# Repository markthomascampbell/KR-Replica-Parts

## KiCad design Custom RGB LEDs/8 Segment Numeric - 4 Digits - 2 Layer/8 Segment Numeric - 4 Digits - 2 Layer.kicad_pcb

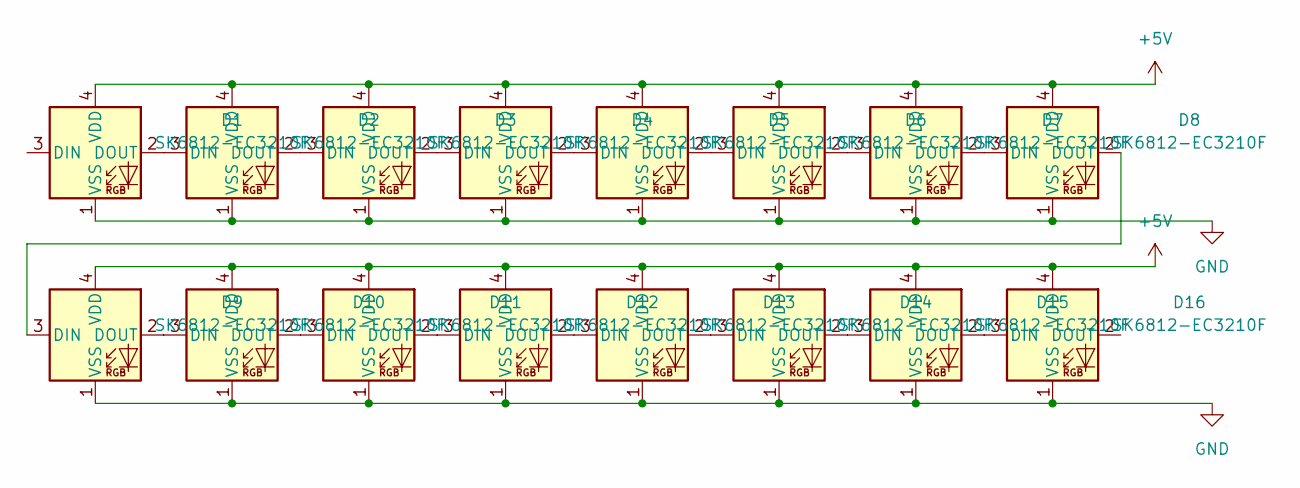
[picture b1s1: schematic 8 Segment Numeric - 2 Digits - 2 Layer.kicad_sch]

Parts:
D1, D2, D3, D4, D5, D6, D7, D8, D9, D10, D11, D12, D13, D14, D15, D16: SK6812-EC3210F

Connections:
+5V: D1.4 (VDD), D2.4 (VDD), D3.4 (VDD), D4.4 (VDD), D5.4 (VDD), D6.4 (VDD), D7.4 (VDD), D8.4 (VDD), D9.4 (VDD), D10.4 (VDD), D11.4 (VDD), D12.4 (VDD), D13.4 (VDD), D14.4 (VDD), D15.4 (VDD), D16.4 (VDD); also elsewhere on the board
GND: D1.1 (VSS), D2.1 (VSS), D3.1 (VSS), D4.1 (VSS), D5.1 (VSS), D6.1 (VSS), D7.1 (VSS), D8.1 (VSS), D9.1 (VSS), D10.1 (VSS), D11.1 (VSS), D12.1 (VSS), D13.1 (VSS), D14.1 (VSS), D15.1 (VSS), D16.1 (VSS); also elsewhere on the board
unnamed: D1.2 (DOUT), D2.3 (DIN)
unnamed: D2.2 (DOUT), D3.3 (DIN)
unnamed: D3.2 (DOUT), D4.3 (DIN)
unnamed: D4.2 (DOUT), D5.3 (DIN)
unnamed: D5.2 (DOUT), D6.3 (DIN)
unnamed: D6.2 (DOUT), D7.3 (DIN)
unnamed: D7.2 (DOUT), D8.3 (DIN)
unnamed: D8.2 (DOUT), D9.3 (DIN)
unnamed: D9.2 (DOUT), D10.3 (DIN)
unnamed: D10.2 (DOUT), D11.3 (DIN)
unnamed: D11.2 (DOUT), D12.3 (DIN)
unnamed: D12.2 (DOUT), D13.3 (DIN)
unnamed: D13.2 (DOUT), D14.3 (DIN)
unnamed: D14.2 (DOUT), D15.3 (DIN)
unnamed: D15.2 (DOUT), D16.3 (DIN)
unnamed 17: D16.2 (DOUT); also elsewhere on the board

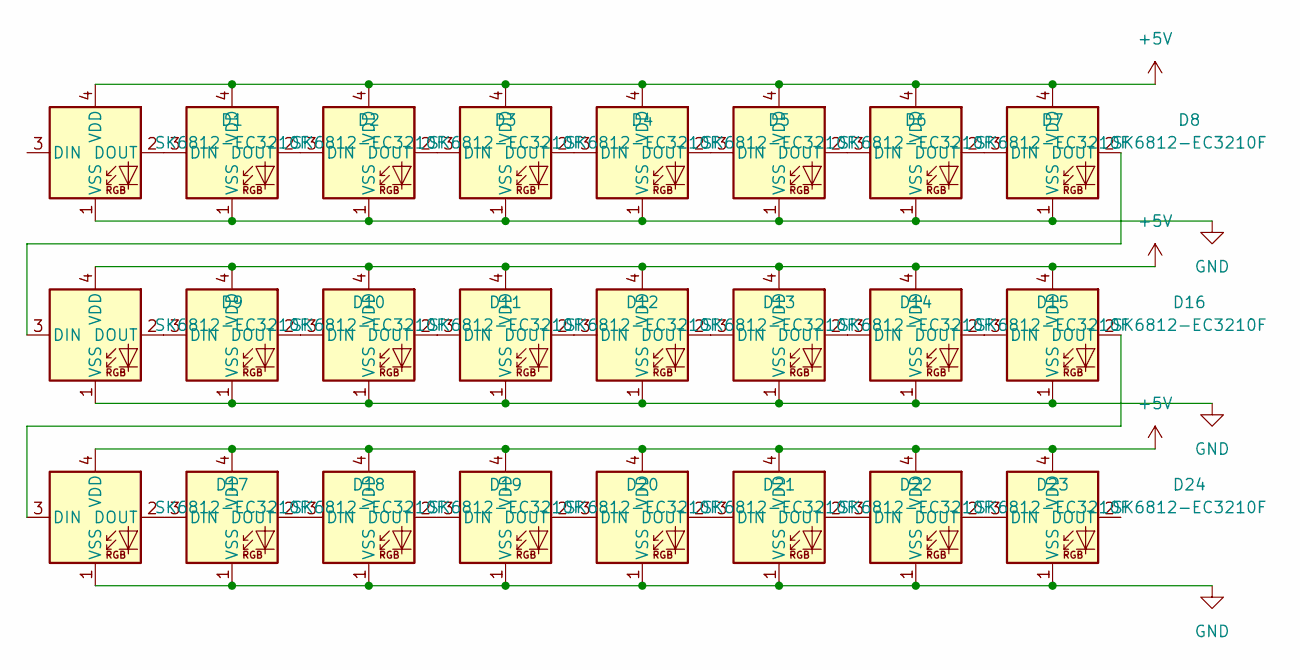
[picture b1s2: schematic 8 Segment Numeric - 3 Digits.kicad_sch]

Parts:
D1, D2, D3, D4, D5, D6, D7, D8, D9, D10, D11, D12, D13, D14, D15, D16, D17, D18, D19, D20, D21, D22, D23, D24: SK6812-EC3210F

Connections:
+5V: D1.4 (VDD), D2.4 (VDD), D3.4 (VDD), D4.4 (VDD), D5.4 (VDD), D6.4 (VDD), D7.4 (VDD), D8.4 (VDD), D9.4 (VDD), D10.4 (VDD), D11.4 (VDD), D12.4 (VDD), D13.4 (VDD), D14.4 (VDD), D15.4 (VDD), D16.4 (VDD), D17.4 (VDD), D18.4 (VDD), D19.4 (VDD), D20.4 (VDD), D21.4 (VDD), D22.4 (VDD), D23.4 (VDD), D24.4 (VDD); also elsewhere on the board
GND: D1.1 (VSS), D2.1 (VSS), D3.1 (VSS), D4.1 (VSS), D5.1 (VSS), D6.1 (VSS), D7.1 (VSS), D8.1 (VSS), D9.1 (VSS), D10.1 (VSS), D11.1 (VSS), D12.1 (VSS), D13.1 (VSS), D14.1 (VSS), D15.1 (VSS), D16.1 (VSS), D17.1 (VSS), D18.1 (VSS), D19.1 (VSS), D20.1 (VSS), D21.1 (VSS), D22.1 (VSS), D23.1 (VSS), D24.1 (VSS); also elsewhere on the board
unnamed: D1.2 (DOUT), D2.3 (DIN)
unnamed: D2.2 (DOUT), D3.3 (DIN)
unnamed: D3.2 (DOUT), D4.3 (DIN)
unnamed: D4.2 (DOUT), D5.3 (DIN)
unnamed: D5.2 (DOUT), D6.3 (DIN)
unnamed: D6.2 (DOUT), D7.3 (DIN)
unnamed: D7.2 (DOUT), D8.3 (DIN)
unnamed: D8.2 (DOUT), D9.3 (DIN)
unnamed: D9.2 (DOUT), D10.3 (DIN)
unnamed: D10.2 (DOUT), D11.3 (DIN)
unnamed: D11.2 (DOUT), D12.3 (DIN)
unnamed: D12.2 (DOUT), D13.3 (DIN)
unnamed: D13.2 (DOUT), D14.3 (DIN)
unnamed: D14.2 (DOUT), D15.3 (DIN)
unnamed: D15.2 (DOUT), D16.3 (DIN)
unnamed: D16.2 (DOUT), D17.3 (DIN)
unnamed: D17.2 (DOUT), D18.3 (DIN)
unnamed: D18.2 (DOUT), D19.3 (DIN)
unnamed: D19.2 (DOUT), D20.3 (DIN)
unnamed: D20.2 (DOUT), D21.3 (DIN)
unnamed: D21.2 (DOUT), D22.3 (DIN)
unnamed: D22.2 (DOUT), D23.3 (DIN)
unnamed: D23.2 (DOUT), D24.3 (DIN)
unnamed 25: D24.2 (DOUT); also elsewhere on the board

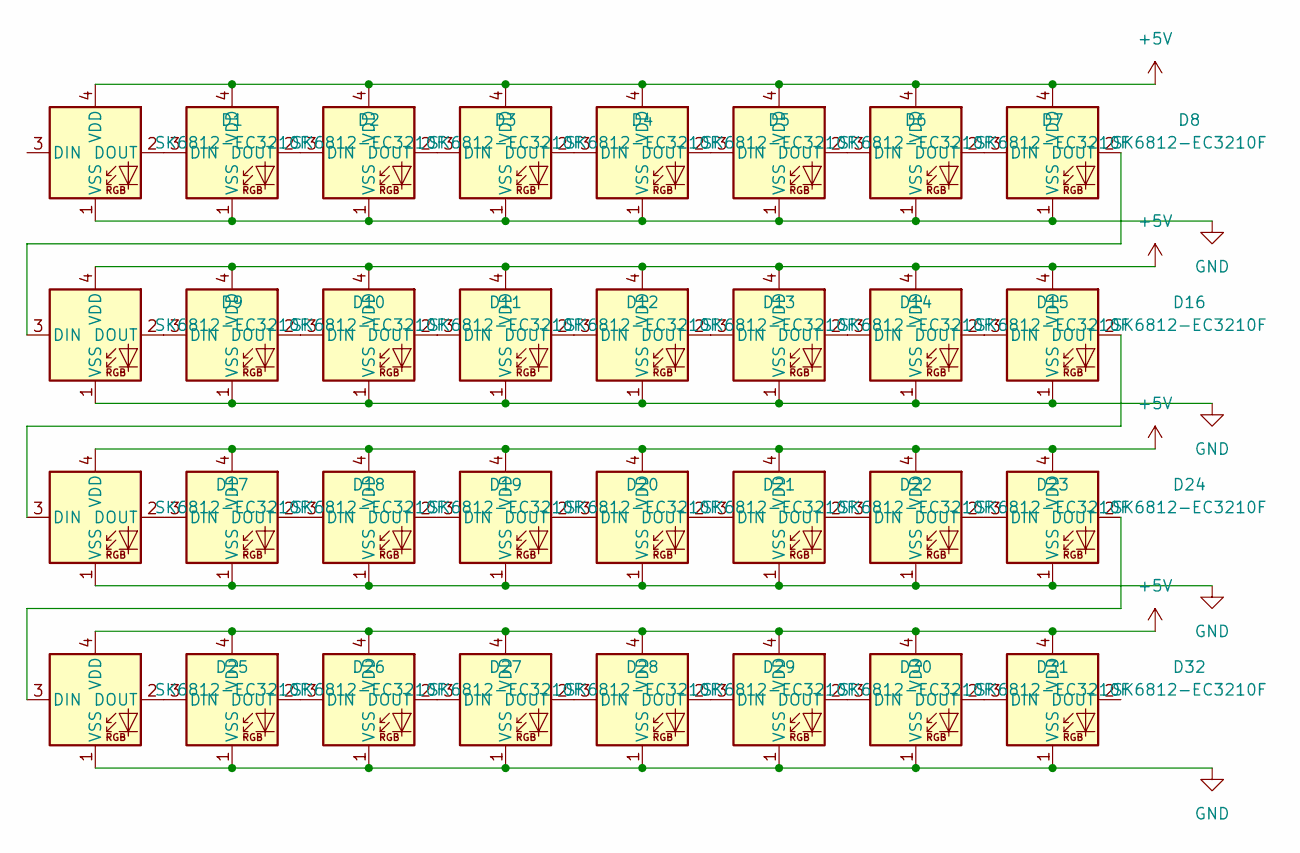
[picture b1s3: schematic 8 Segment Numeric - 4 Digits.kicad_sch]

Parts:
D1, D2, D3, D4, D5, D6, D7, D8, D9, D10, D11, D12, D13, D14, D15, D16, D17, D18, D19, D20, D21, D22, D23, D24, D25, D26, D27, D28, D29, D30, D31, D32: SK6812-EC3210F

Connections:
+5V: D1.4 (VDD), D2.4 (VDD), D3.4 (VDD), D4.4 (VDD), D5.4 (VDD), D6.4 (VDD), D7.4 (VDD), D8.4 (VDD), D9.4 (VDD), D10.4 (VDD), D11.4 (VDD), D12.4 (VDD), D13.4 (VDD), D14.4 (VDD), D15.4 (VDD), D16.4 (VDD), D17.4 (VDD), D18.4 (VDD), D19.4 (VDD), D20.4 (VDD), D21.4 (VDD), D22.4 (VDD), D23.4 (VDD), D24.4 (VDD), D25.4 (VDD), D26.4 (VDD), D27.4 (VDD), D28.4 (VDD), D29.4 (VDD), D30.4 (VDD), D31.4 (VDD), D32.4 (VDD); also elsewhere on the board
GND: D1.1 (VSS), D2.1 (VSS), D3.1 (VSS), D4.1 (VSS), D5.1 (VSS), D6.1 (VSS), D7.1 (VSS), D8.1 (VSS), D9.1 (VSS), D10.1 (VSS), D11.1 (VSS), D12.1 (VSS), D13.1 (VSS), D14.1 (VSS), D15.1 (VSS), D16.1 (VSS), D17.1 (VSS), D18.1 (VSS), D19.1 (VSS), D20.1 (VSS), D21.1 (VSS), D22.1 (VSS), D23.1 (VSS), D24.1 (VSS), D25.1 (VSS), D26.1 (VSS), D27.1 (VSS), D28.1 (VSS), D29.1 (VSS), D30.1 (VSS), D31.1 (VSS), D32.1 (VSS); also elsewhere on the board
unnamed: D1.2 (DOUT), D2.3 (DIN)
unnamed: D2.2 (DOUT), D3.3 (DIN)
unnamed: D3.2 (DOUT), D4.3 (DIN)
unnamed: D4.2 (DOUT), D5.3 (DIN)
unnamed: D5.2 (DOUT), D6.3 (DIN)
unnamed: D6.2 (DOUT), D7.3 (DIN)
unnamed: D7.2 (DOUT), D8.3 (DIN)
unnamed: D8.2 (DOUT), D9.3 (DIN)
unnamed: D9.2 (DOUT), D10.3 (DIN)
unnamed: D10.2 (DOUT), D11.3 (DIN)
unnamed: D11.2 (DOUT), D12.3 (DIN)
unnamed: D12.2 (DOUT), D13.3 (DIN)
unnamed: D13.2 (DOUT), D14.3 (DIN)
unnamed: D14.2 (DOUT), D15.3 (DIN)
unnamed: D15.2 (DOUT), D16.3 (DIN)
unnamed: D16.2 (DOUT), D17.3 (DIN)
unnamed: D17.2 (DOUT), D18.3 (DIN)
unnamed: D18.2 (DOUT), D19.3 (DIN)
unnamed: D19.2 (DOUT), D20.3 (DIN)
unnamed: D20.2 (DOUT), D21.3 (DIN)
unnamed: D21.2 (DOUT), D22.3 (DIN)
unnamed: D22.2 (DOUT), D23.3 (DIN)
unnamed: D23.2 (DOUT), D24.3 (DIN)
unnamed: D24.2 (DOUT), D25.3 (DIN)
unnamed: D25.2 (DOUT), D26.3 (DIN)
unnamed: D26.2 (DOUT), D27.3 (DIN)
unnamed: D27.2 (DOUT), D28.3 (DIN)
unnamed: D28.2 (DOUT), D29.3 (DIN)
unnamed: D29.2 (DOUT), D30.3 (DIN)
unnamed: D30.2 (DOUT), D31.3 (DIN)
unnamed: D31.2 (DOUT), D32.3 (DIN)

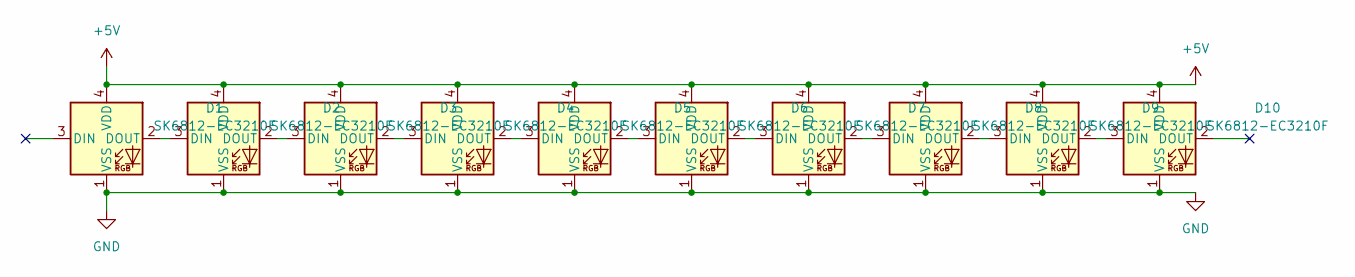
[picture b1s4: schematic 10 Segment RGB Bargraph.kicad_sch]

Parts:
D1, D2, D3, D4, D5, D6, D7, D8, D9, D10: SK6812-EC3210F

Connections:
+5V: D1.4 (VDD), D2.4 (VDD), D3.4 (VDD), D4.4 (VDD), D5.4 (VDD), D6.4 (VDD), D7.4 (VDD), D8.4 (VDD), D9.4 (VDD), D10.4 (VDD); also elsewhere on the board
GND: D1.1 (VSS), D2.1 (VSS), D3.1 (VSS), D4.1 (VSS), D5.1 (VSS), D6.1 (VSS), D7.1 (VSS), D8.1 (VSS), D9.1 (VSS), D10.1 (VSS); also elsewhere on the board
unnamed: D1.2 (DOUT), D2.3 (DIN)
unnamed: D2.2 (DOUT), D3.3 (DIN)
unnamed: D3.2 (DOUT), D4.3 (DIN)
unnamed: D4.2 (DOUT), D5.3 (DIN)
unnamed: D5.2 (DOUT), D6.3 (DIN)
unnamed: D6.2 (DOUT), D7.3 (DIN)
unnamed: D7.2 (DOUT), D8.3 (DIN)
unnamed: D8.2 (DOUT), D9.3 (DIN)
unnamed: D9.2 (DOUT), D10.3 (DIN)
unnamed 11: D10.2 (DOUT); also elsewhere on the board

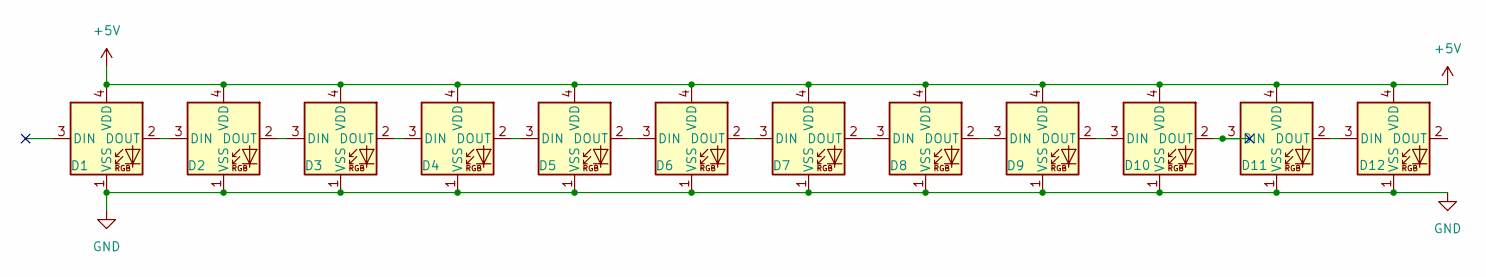
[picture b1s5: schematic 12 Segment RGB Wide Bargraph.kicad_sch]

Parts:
D1, D2, D3, D4, D5, D6, D7, D8, D9, D10, D11, D12: SK6812-EC3210F

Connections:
+5V: D1.4 (VDD), D2.4 (VDD), D3.4 (VDD), D4.4 (VDD), D5.4 (VDD), D6.4 (VDD), D7.4 (VDD), D8.4 (VDD), D9.4 (VDD), D10.4 (VDD), D11.4 (VDD), D12.4 (VDD); also elsewhere on the board
GND: D1.1 (VSS), D2.1 (VSS), D3.1 (VSS), D4.1 (VSS), D5.1 (VSS), D6.1 (VSS), D7.1 (VSS), D8.1 (VSS), D9.1 (VSS), D10.1 (VSS), D11.1 (VSS), D12.1 (VSS); also elsewhere on the board
unnamed: D1.2 (DOUT), D2.3 (DIN)
unnamed: D2.2 (DOUT), D3.3 (DIN)
unnamed: D3.2 (DOUT), D4.3 (DIN)
unnamed: D4.2 (DOUT), D5.3 (DIN)
unnamed: D5.2 (DOUT), D6.3 (DIN)
unnamed: D6.2 (DOUT), D7.3 (DIN)
unnamed: D7.2 (DOUT), D8.3 (DIN)
unnamed: D8.2 (DOUT), D9.3 (DIN)
unnamed: D9.2 (DOUT), D10.3 (DIN)
unnamed: D10.2 (DOUT), D11.3 (DIN)
unnamed: D11.2 (DOUT), D12.3 (DIN)
unnamed 13: D12.2 (DOUT); also elsewhere on the board

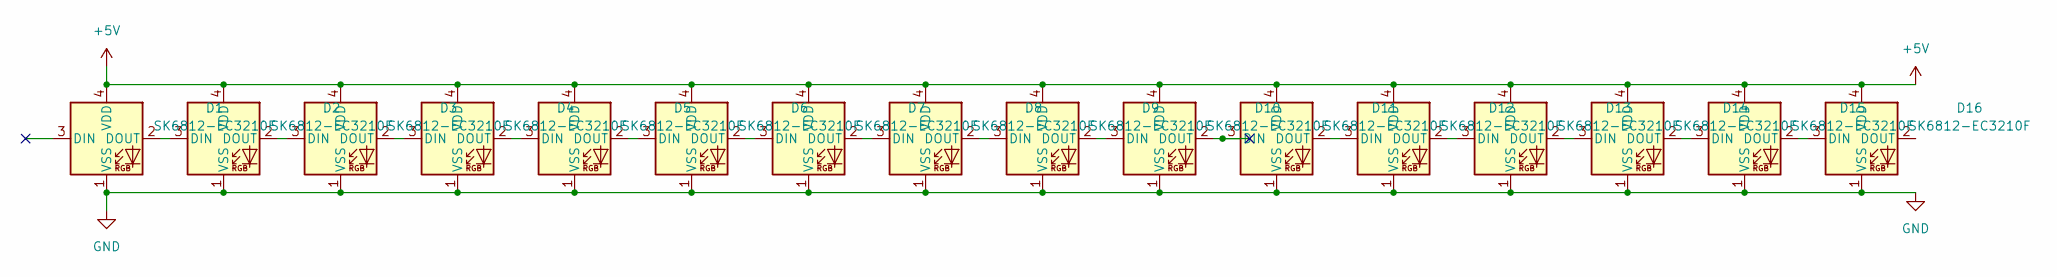
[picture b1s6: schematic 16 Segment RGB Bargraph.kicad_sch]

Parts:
D1, D2, D3, D4, D5, D6, D7, D8, D9, D10, D11, D12, D13, D14, D15, D16: SK6812-EC3210F

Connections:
+5V: D1.4 (VDD), D2.4 (VDD), D3.4 (VDD), D4.4 (VDD), D5.4 (VDD), D6.4 (VDD), D7.4 (VDD), D8.4 (VDD), D9.4 (VDD), D10.4 (VDD), D11.4 (VDD), D12.4 (VDD), D13.4 (VDD), D14.4 (VDD), D15.4 (VDD), D16.4 (VDD); also elsewhere on the board
GND: D1.1 (VSS), D2.1 (VSS), D3.1 (VSS), D4.1 (VSS), D5.1 (VSS), D6.1 (VSS), D7.1 (VSS), D8.1 (VSS), D9.1 (VSS), D10.1 (VSS), D11.1 (VSS), D12.1 (VSS), D13.1 (VSS), D14.1 (VSS), D15.1 (VSS), D16.1 (VSS); also elsewhere on the board
unnamed: D1.2 (DOUT), D2.3 (DIN)
unnamed: D2.2 (DOUT), D3.3 (DIN)
unnamed: D3.2 (DOUT), D4.3 (DIN)
unnamed: D4.2 (DOUT), D5.3 (DIN)
unnamed: D5.2 (DOUT), D6.3 (DIN)
unnamed: D6.2 (DOUT), D7.3 (DIN)
unnamed: D7.2 (DOUT), D8.3 (DIN)
unnamed: D8.2 (DOUT), D9.3 (DIN)
unnamed: D9.2 (DOUT), D10.3 (DIN)
unnamed: D10.2 (DOUT), D11.3 (DIN)
unnamed: D11.2 (DOUT), D12.3 (DIN)
unnamed: D12.2 (DOUT), D13.3 (DIN)
unnamed: D13.2 (DOUT), D14.3 (DIN)
unnamed: D14.2 (DOUT), D15.3 (DIN)
unnamed: D15.2 (DOUT), D16.3 (DIN)
unnamed 17: D16.2 (DOUT); also elsewhere on the board

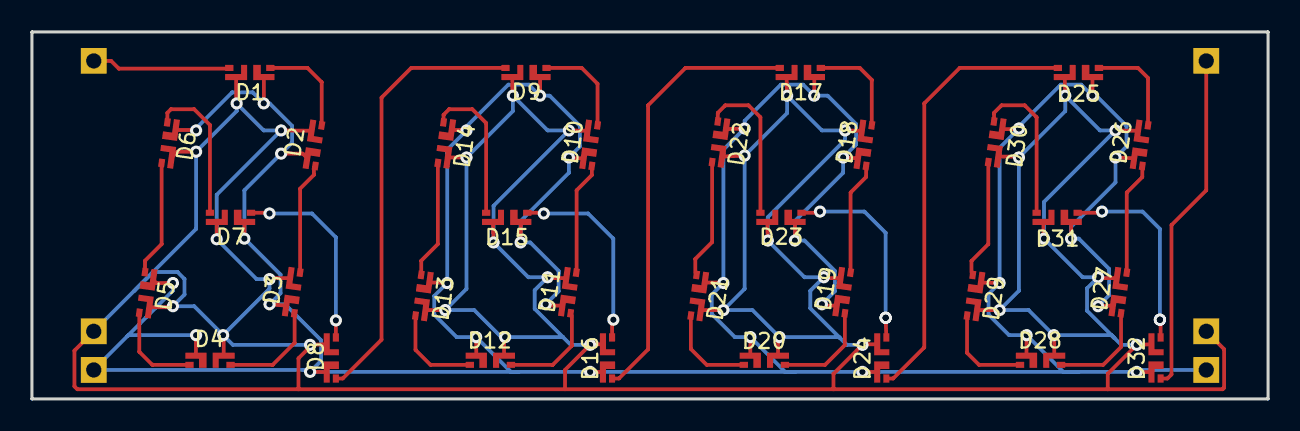
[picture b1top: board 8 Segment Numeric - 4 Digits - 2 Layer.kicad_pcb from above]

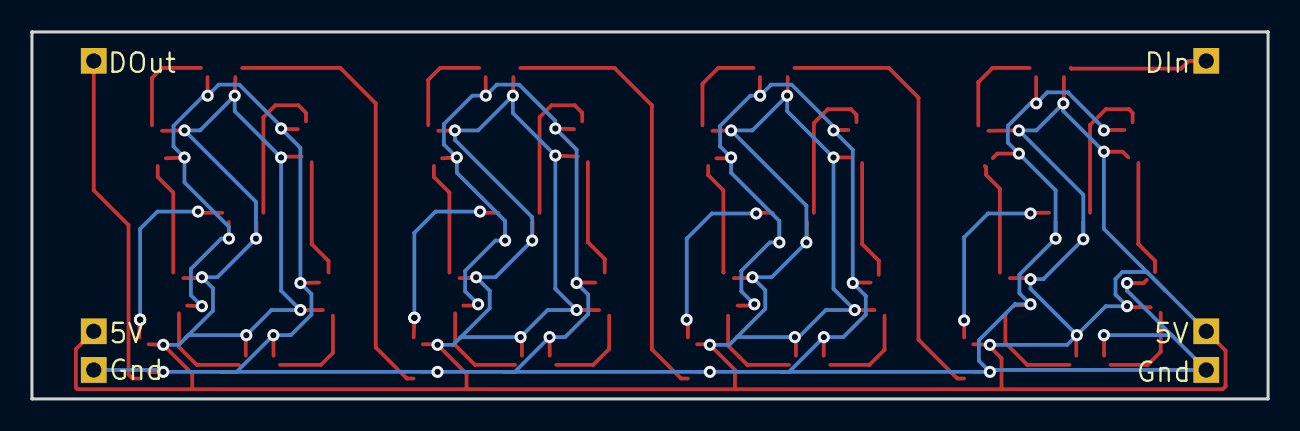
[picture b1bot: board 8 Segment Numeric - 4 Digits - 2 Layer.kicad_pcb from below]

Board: 2 copper layers, 81.3 x 24.1 mm, 34 parts (2 on the bottom side), 33 nets.

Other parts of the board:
5V: (no value)
Gnd: (no value)

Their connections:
+5V: 5V.1; also elsewhere on the board
GND: Gnd.1; also elsewhere on the board

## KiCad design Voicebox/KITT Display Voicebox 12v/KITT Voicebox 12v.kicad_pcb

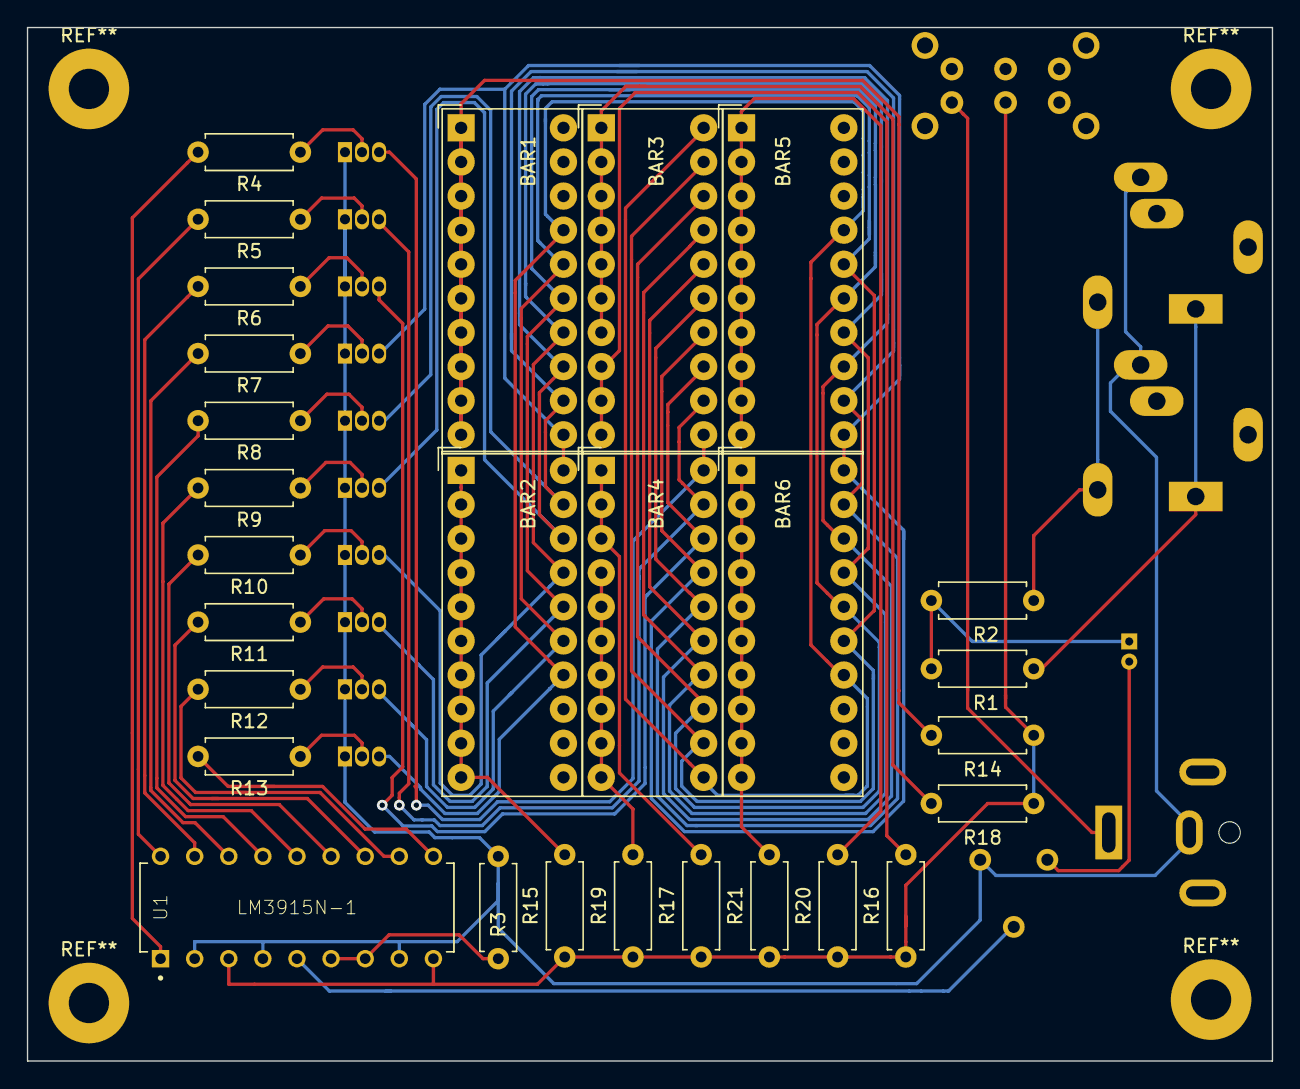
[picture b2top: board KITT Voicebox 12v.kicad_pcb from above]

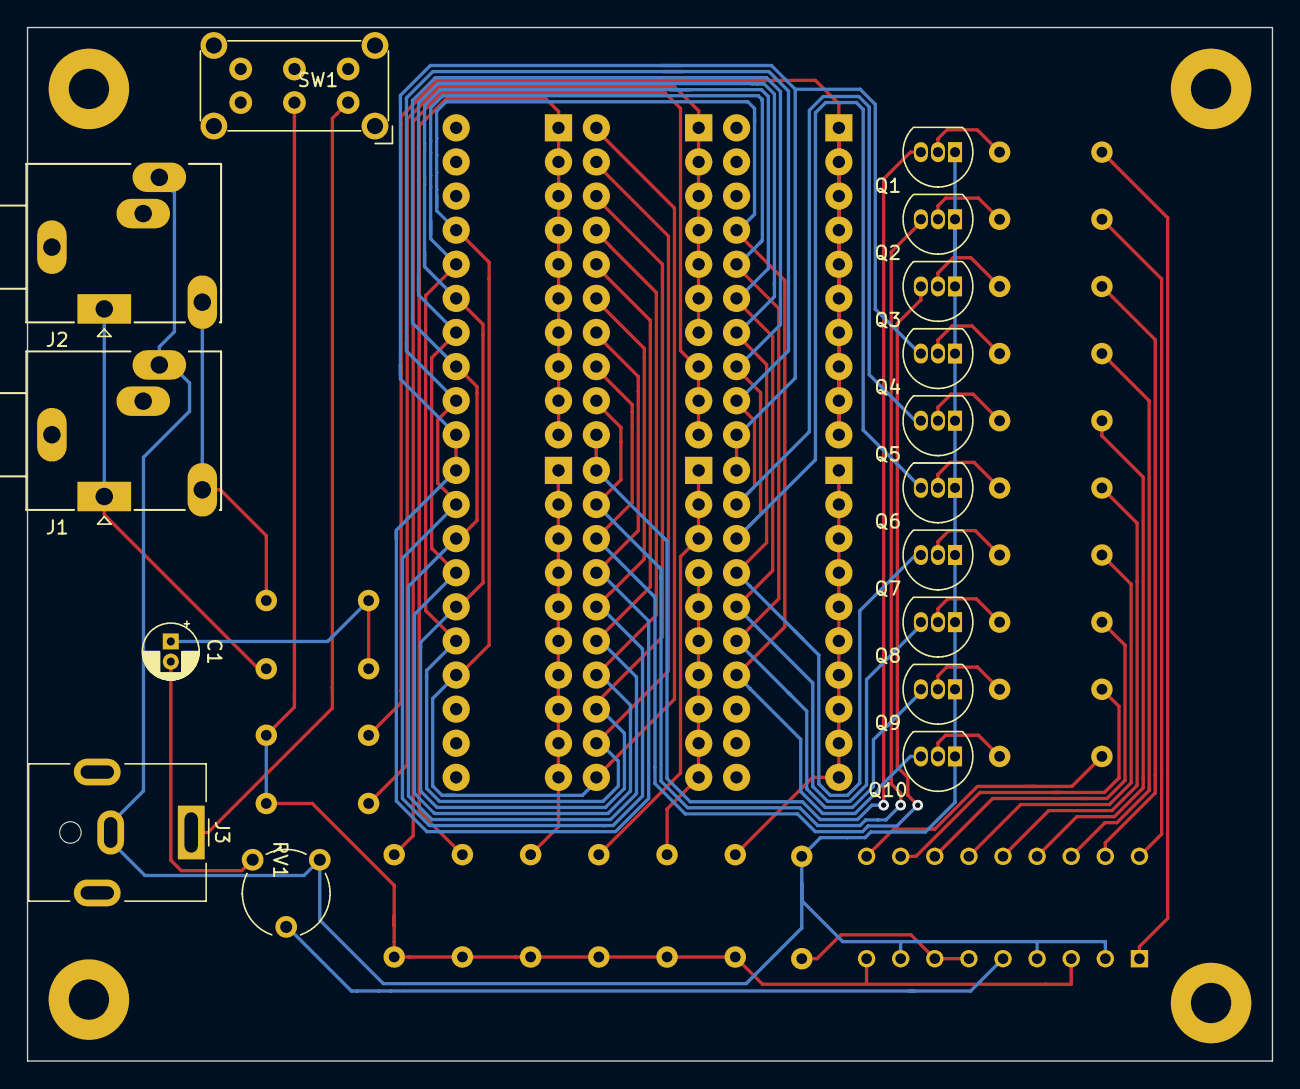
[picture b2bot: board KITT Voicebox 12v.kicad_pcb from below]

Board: 2 copper layers, 92.7 x 77.0 mm, 44 parts (16 on the bottom side), 47 nets.

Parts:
BAR1, BAR2, BAR3, BAR4, BAR5, BAR6: LED_BAR; HLCP-J100
C1: 1uF; CP_Radial_D4.0mm_P1.50mm
J1: Audio In; StereoJack_3.5mm_Switch_Ledino_KB3SPRS_Horizontal
J2: Audio Out; StereoJack_3.5mm_Switch_Ledino_KB3SPRS_Horizontal
J3: Power IN; BarrelJack_CUI_PJ-063AH_Horizontal
Q1, Q2, Q3, Q4, Q5, Q6, Q7, Q8, Q9, Q10: BC557; TO-92_Inline
R1, R2, R3, R4, R5, R6, R7, R8, R9, R10, R11, R12, R13: 1k; R_Axial_DIN0207_L6.3mm_D2.5mm_P7.62mm_Horizontal
R14, R15, R18, R19, R20, R21: 180R; R_Axial_DIN0207_L6.3mm_D2.5mm_P7.62mm_Horizontal
R16, R17: 150R; R_Axial_DIN0207_L6.3mm_D2.5mm_P7.62mm_Horizontal
RV1: 10k; Potentiometer_Piher_PT-6-V_Vertical
SW1: SW_SPST; SW_E-Switch_EG2219_DPDT_Angled
U1: LM3915N-1; DIP795W25P254L2337H533Q18B

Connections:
unnamed: BAR1.1, BAR1.2, BAR1.3, BAR1.4, BAR1.5, BAR1.6, BAR1.7, BAR1.8, BAR1.9, BAR1.10, R14.2
unnamed: BAR1.11, BAR2.20, BAR3.14, BAR4.17, BAR5.11, BAR6.20, Q4.3
unnamed: BAR1.12, BAR2.19, BAR3.15, BAR4.16, BAR5.12, BAR6.19, Q5.3
unnamed: BAR1.13, BAR2.18, BAR3.16, BAR4.15, BAR5.13, BAR6.18, Q6.3
unnamed: BAR1.14, BAR2.17, BAR3.17, BAR4.14, BAR5.14, BAR6.17, Q7.3
unnamed: BAR1.15, BAR2.16, BAR3.18, BAR4.13, BAR5.15, BAR6.16, Q8.3
unnamed: BAR1.16, BAR2.15, BAR3.19, BAR4.12, BAR5.16, BAR6.15, Q9.3
unnamed: BAR1.17, BAR2.14, BAR3.20, BAR4.11, BAR5.17, BAR6.14, Q10.3
unnamed: BAR2.1, BAR2.2, BAR2.3, BAR2.4, BAR2.5, BAR2.6, BAR2.7, BAR2.8, BAR2.9, BAR2.10, R15.1
unnamed: BAR3.1, BAR3.2, BAR3.3, BAR3.4, BAR3.5, BAR3.6, BAR3.7, R18.2
unnamed: BAR3.8, BAR3.9, BAR3.10, R16.2
unnamed: BAR3.11, BAR4.20, Q1.3
unnamed: BAR3.12, BAR4.19, Q2.3
unnamed: BAR3.13, BAR4.18, Q3.3
unnamed: BAR4.1, BAR4.2, BAR4.3, R17.1
unnamed: BAR4.4, BAR4.5, BAR4.6, BAR4.7, BAR4.8, BAR4.9, BAR4.10, R19.1
unnamed: BAR5.1, BAR5.2, BAR5.3, BAR5.4, BAR5.5, BAR5.6, BAR5.7, BAR5.8, BAR5.9, BAR5.10, R20.2
unnamed: BAR6.1, BAR6.2, BAR6.3, BAR6.4, BAR6.5, BAR6.6, BAR6.7, BAR6.8, BAR6.9, BAR6.10, R21.1
unnamed: C1.1, R1.1, R2.1
unnamed: C1.2, RV1.1
unnamed: J1.1, J2.1, R1.2
unnamed: J1.2, J2.2, J3.2, Q1.1, Q2.1, Q3.1, Q4.1, Q5.1, Q6.1, Q7.1, Q8.1, Q9.1, Q10.1, R3.2, RV1.3, U1.2, U1.4, U1.8
unnamed: J1.4, J2.4, R2.2
unnamed: J3.1, SW1.1
unnamed: Q1.2, R4.1
unnamed: Q2.2, R5.1
unnamed: Q3.2, R6.1
unnamed: Q4.2, R7.1
unnamed: Q5.2, R8.1
unnamed: Q6.2, R9.1
unnamed: Q7.2, R10.1
unnamed: Q8.2, R11.1
unnamed: Q9.2, R12.1
unnamed: Q10.2, R13.1
unnamed: R3.1, U1.6, U1.7
unnamed: R4.2, U1.1
unnamed: R5.2, U1.18
unnamed: R6.2, U1.17
unnamed: R7.2, U1.16
unnamed: R8.2, U1.15
unnamed: R9.2, U1.14
unnamed: R10.2, U1.13
unnamed: R11.2, U1.12
unnamed: R12.2, U1.11
unnamed: R13.2, U1.10
unnamed: R14.1, R15.2, R16.1, R17.2, R18.1, R19.2, R20.1, R21.2, SW1.2, U1.3, U1.9
unnamed: RV1.2, U1.5
